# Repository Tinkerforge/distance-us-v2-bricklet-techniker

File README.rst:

Distance US Bricklet 2.0
========================

**This Bricklet is currently in development.**

This repository contains the firmware source code and the hardware design
files. The documentation generator configs can be found at
https://github.com/Tinkerforge/generators

Repository Content
------------------

software/:
 * examples/: Examples for all supported languages
 * build/: Compiled files
 * src/: Source code of firmware
 * Makefile: Makefile to build project

hardware/:
 * Contains KiCad project files and additionally schematics as PDF

datasheets/:
 * Contains datasheets for sensors and complex ICs that are used

Hardware
--------

The hardware is designed with the open source EDA Suite KiCad
(http://www.kicad.org). Before you are able to open the files,
you have to install the Tinkerforge kicad-libraries
(https://github.com/Tinkerforge/kicad-libraries). You can either clone
them directly in hardware/ or clone them in a separate folder and
symlink them into hardware/
(ln -s kicad_path/kicad-libraries project_path/hardware). After that you
can open the .pro file in hardware/ with KiCad and from there view and
modify the schematics and the PCB layout.

Software
--------

If you want to do your own Brick/Bricklet firmware development we highly
recommend that you use our build environment setup script and read the
tutorial (https://www.tinkerforge.com/en/doc/Tutorials/Tutorial_Build_Environment/Tutorial.html).

To compile the C code we recommend you to install the newest GNU Arm Embedded
Toolchain (https://launchpad.net/gcc-arm-embedded/+download).
You also need to install bricklib2 (https://github.com/Tinkerforge/bricklib2).

You can either clone it directly in software/src/ or clone it in a
separate folder and symlink it into software/src/
(ln -s bricklib_path/bricklib2 project_path/software/src/). Finally make sure to
have CMake installed (http://www.cmake.org/cmake/resources/software.html).

After that you can build the firmware by invoking make in software/.
The firmware (.zbin) can then be found in software/build/ and uploaded
with brickv (click button "Flashing" on start screen).

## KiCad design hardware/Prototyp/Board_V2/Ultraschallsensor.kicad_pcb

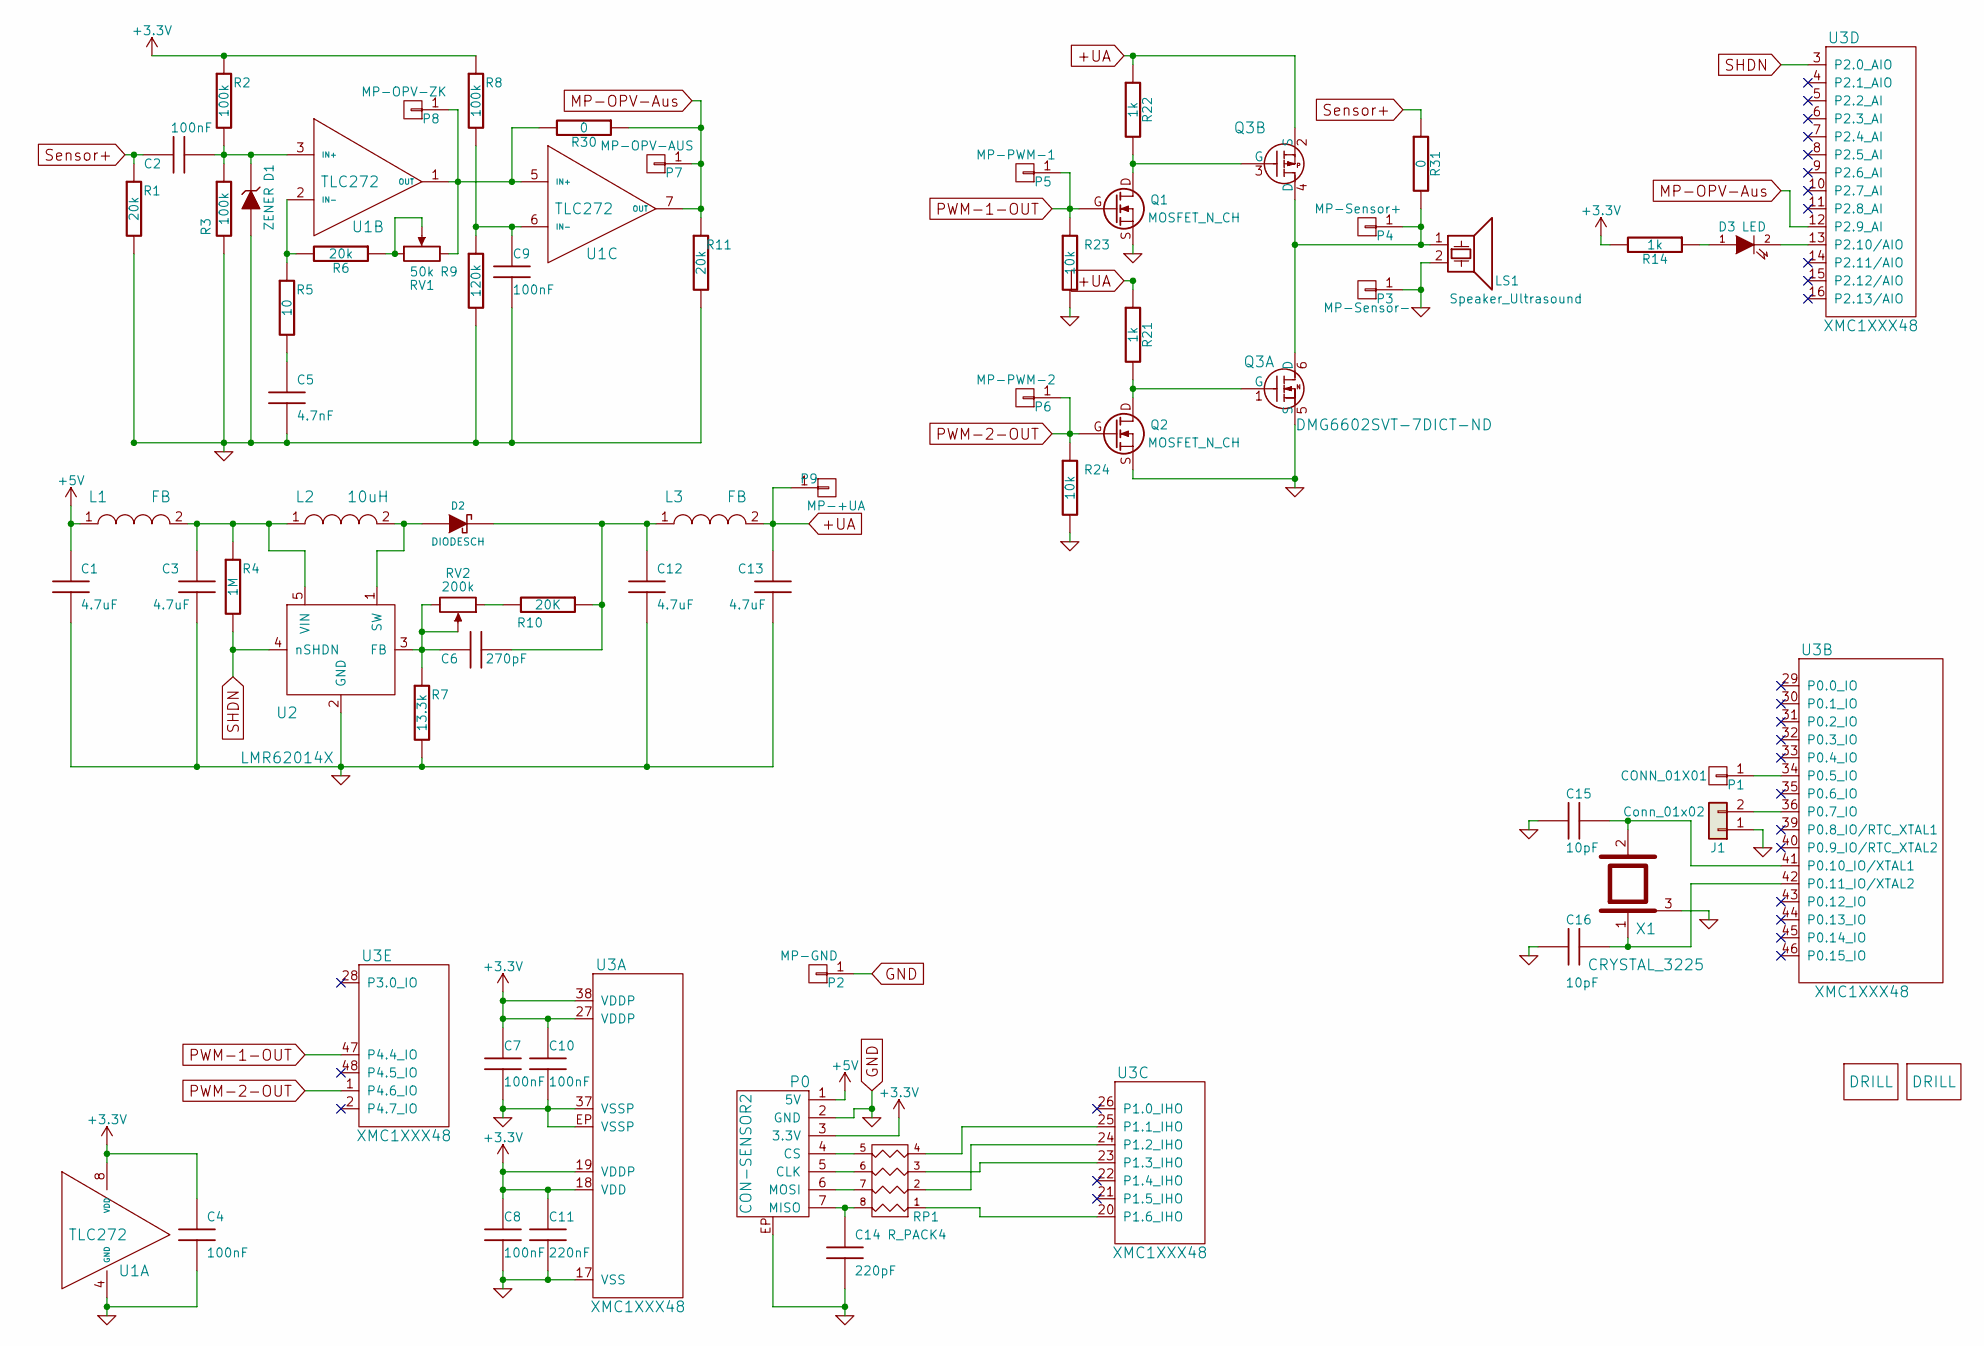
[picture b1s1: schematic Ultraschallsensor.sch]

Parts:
C1, C3, C12, C13: 4.7uF; C0805
C2, C4, C7, C8, C9, C10: 100nF; C0603F
C5: 4.7nF; C0603F
C6: 270pF; C0603F
C11: 220nF; C0603F
C14: 220pF; C0402F
C15, C16: 10pF; C0603F
D1: ZENER; SOD-123
D2: DIODESCH; SOD-123
D3: LED; D0603E
J1: Conn_01x02; SolderJumper
L1, L3: FB; C0603F
L2: 10uH; NR3030
LS1: Speaker_Ultrasound; PIN_ARRAY_2X1
P0: CON-SENSOR2
P1: CONN_01X01; CONN_1
P2: MP-GND; CONN_1
P3: MP-Sensor-; DEBUG_PAD
P4: MP-Sensor+; DEBUG_PAD
P5: MP-PWM-1; DEBUG_PAD
P6: MP-PWM-2; DEBUG_PAD
P7: MP-OPV-AUS; CONN_1
P8: MP-OPV-ZK; CONN_1
P9: MP-+UA; CONN_1
Q1, Q2: MOSFET_N_CH; SOT23GDS
Q3: DMG6602SVT-7DICT-ND; SOT23-6
R1, R6, R11: 20k; R0603F
R2, R3, R8: 100k; R0603F
R4: 1M; R0603F
R5: 10; R0603F
R7: 13.3k; R0603F
R9: 120k; R0603F
R10: 20K; R0603F
R14: 1k; R0603F
R21, R22: 1k; 1206E
R23, R24: 10k; R0603F
R30, R31: 0; R0603F
RP1: R_PACK4; 4X0402
RV1: 50k; ST4
RV2: 200k; ST4
U1: TLC272; TSSOP8
U2: LMR62014X; SOT23-5
U3: XMC1XXX48; QFN48-EP2
U4, U5: DRILL; DRILL_NP
X1: CRYSTAL_3225

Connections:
+3V3: C4.1, C7.1, C8.1, C10.1, C11.1, P0.3 (3.3V), R2.1, R8.1, R14.2, U1.8 (VDD), U3.18 (VDD), U3.19 (VDDP), U3.27 (VDDP), U3.38 (VDDP)
+5V: C1.1, L1.1, P0.1 (5V)
+UA: C13.1, L3.2, P9.1, Q3.2 (S), R21.1, R22.1
GND: C1.2, C3.2, C4.2, C5.2, C7.2, C8.2, C9.2, C10.2, C11.2, C12.2, C13.2, C14.2, C15.2, C16.2, D1.1 (A), J1.1, LS1.2, P0.2 (GND), P0.EP, P2.1, P3.1, Q1.S, Q2.S, Q3.5 (S), R1.2, R3.2, R7.2, R9.2, R11.2, R23.2, R24.2, U1.4 (GND), U2.2 (GND), U3.17 (VSS), U3.37 (VSSP), U3.EP (VSSP), X1.3
MP-OPV-Aus: P7.1, R11.1, R30.1, U1.7 (OUT), U3.12 (P2.9_AI)
unnamed: C2.1, D1.2 (K), R2.2, R3.1, U1.3 (IN+)
unnamed: C3.1, L1.2, L2.1, R4.1, U2.5 (VIN)
unnamed: C5.1, R5.2
unnamed: C6.2, R7.1, RV2.2, RV2.3, U2.3 (FB)
unnamed: C9.1, R8.2, R9.1, U1.6 (IN-)
unnamed: C6.1, C12.1, D2.2 (K), L3.1, R10.1
unnamed: C14.1, P0.7 (MISO), RP1.8 (R1)
unnamed: C15.1, U3.41 (P0.10_IO/XTAL1), X1.2
unnamed: C16.1, U3.42 (P0.11_IO/XTAL2), X1.1
unnamed: D2.1 (A), L2.2, U2.1 (SW)
unnamed: D3.1 (A), R14.1
unnamed: D3.2 (K), U3.13 (P2.10/AIO)
unnamed: J1.2, U3.36 (P0.7_IO)
unnamed: LS1.1, P4.1, Q3.4 (D), Q3.6 (D), R31.2
unnamed: P0.4 (CS), RP1.5 (R4)
unnamed: P0.5 (CLK), RP1.6 (R3)
unnamed: P0.6 (MOSI), RP1.7 (R2)
unnamed: P1.1, U3.34 (P0.5_IO)
unnamed: P8.1, R30.2, RV1.3, U1.1 (OUT), U1.5 (IN+)
unnamed: Q1.D, Q3.3 (G), R22.2
unnamed: Q2.D, Q3.1 (G), R21.2
unnamed: R5.1, R6.2, U1.2 (IN-)
unnamed: R6.1, RV1.1, RV1.2
unnamed: R10.2, RV2.1
unnamed: RP1.1, U3.20 (P1.6_IHO)
unnamed: RP1.2, U3.24 (P1.2_IHO)
unnamed: RP1.3, U3.23 (P1.3_IHO)
unnamed: RP1.4, U3.25 (P1.1_IHO)
PWM-1-OUT: P5.1, Q1.G, R23.1, U3.47 (P4.4_IO)
PWM-2-OUT: P6.1, Q2.G, R24.1, U3.1 (P4.6_IO)
SHDN: R4.2, U2.4 (nSHDN), U3.3 (P2.0_AIO)
Sensor+: C2.2, R1.1, R31.1

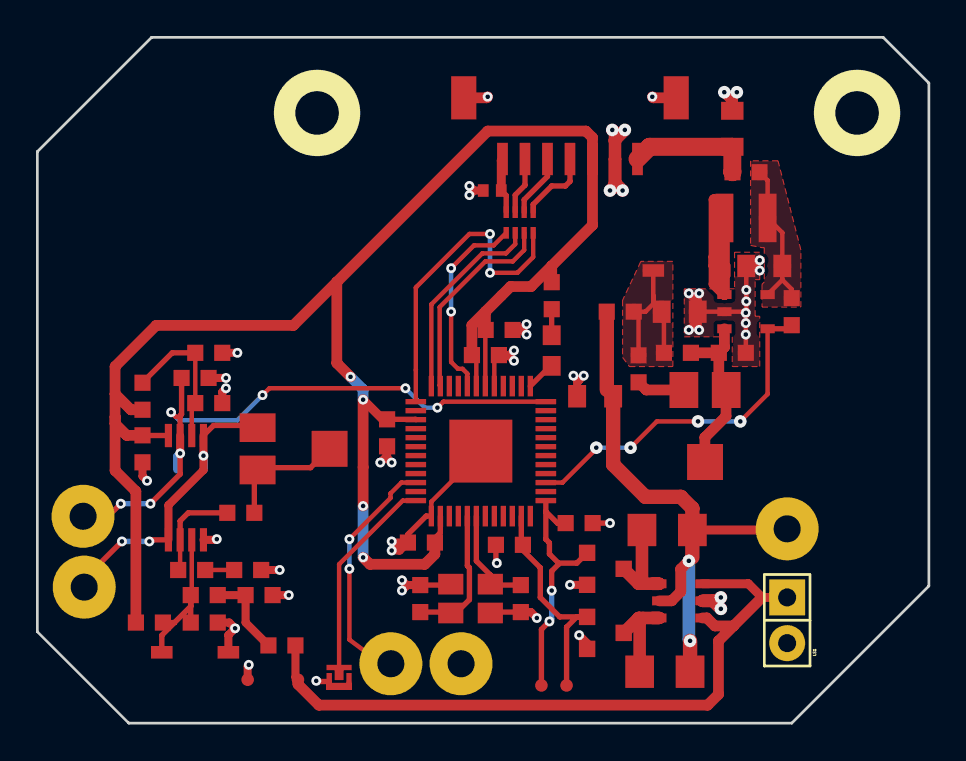
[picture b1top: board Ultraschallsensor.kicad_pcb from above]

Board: 2 copper layers, 49.5 x 38.1 mm, 64 parts (1 on the bottom side), 37 nets.

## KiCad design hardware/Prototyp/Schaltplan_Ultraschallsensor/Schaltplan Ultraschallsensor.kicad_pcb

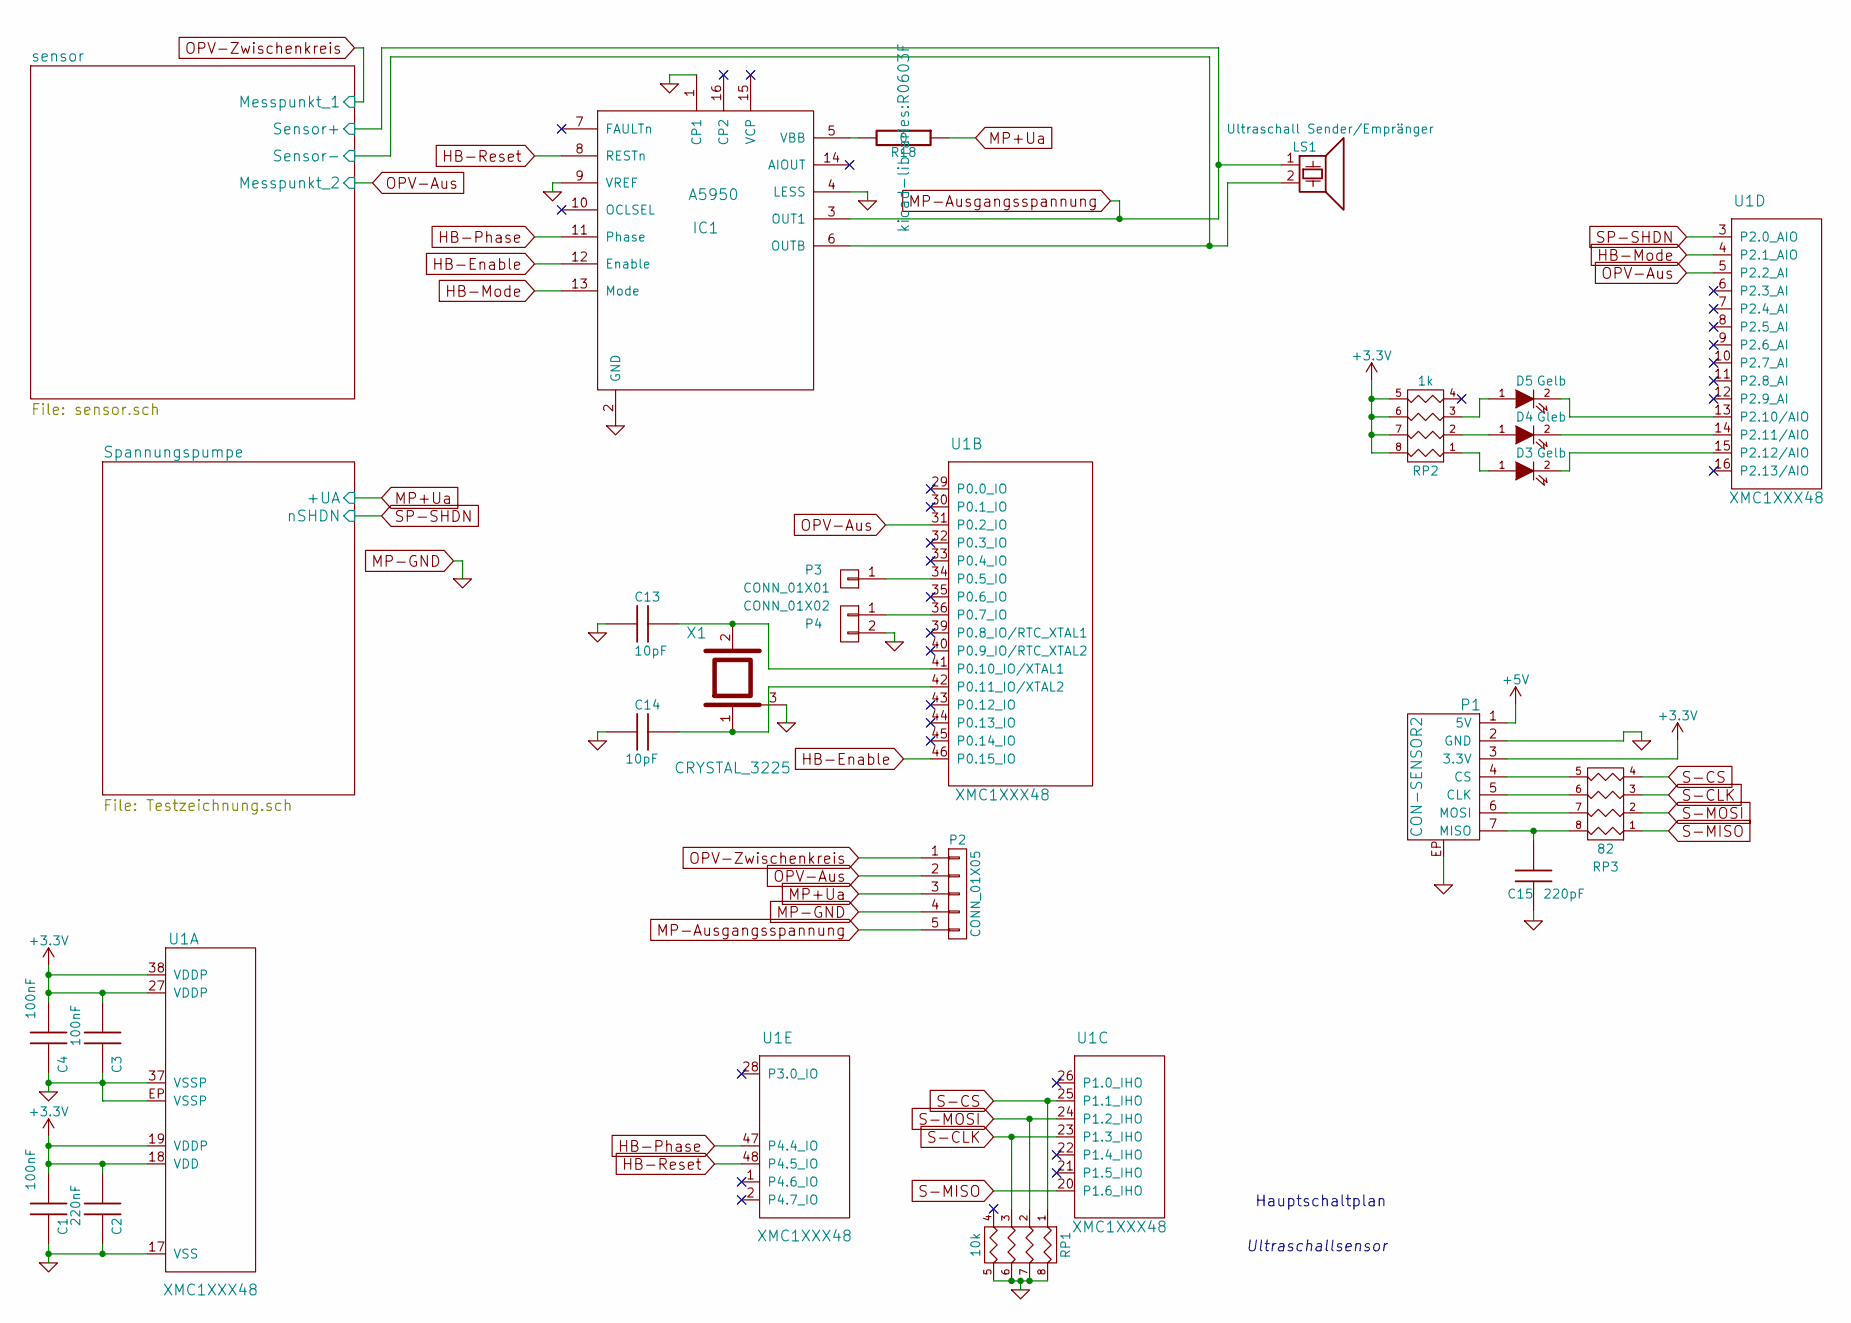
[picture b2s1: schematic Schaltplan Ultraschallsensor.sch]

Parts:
C1, C3, C4: 100nF; C0603F
C2: 220nF; C0603F
C13, C14: 10pF; C0603F
C15: 220pF; C0402F
D3, D5: Gelb; D0603E
D4: Gleb; D0603E
IC1: A5950; 16-leadTSSOP_0,137,4,4mmBreite
LS1: Ultraschall Sender/Empränger; Ultraschallsensor
P1: CON-SENSOR2
P2: CONN_01X05; pin_array_5x1
P3: CONN_01X01; DEBUG_PAD
P4: CONN_01X02; SolderJumper
R18: 0; R0603F
RP1: 10k; 0603X4
RP2: 1k; 0603X4
RP3: 82; 4X0402
U1: XMC1XXX48; QFN48-EP2
X1: CRYSTAL_3225

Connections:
+3V3: C1.1, C2.1, C3.1, C4.1, P1.3 (3.3V), RP2.5 (R4), RP2.6 (R3), RP2.7 (R2), RP2.8 (R1), U1.18 (VDD), U1.19 (VDDP), U1.27 (VDDP), U1.38 (VDDP); also elsewhere on the board
+5V: P1.1 (5V); also elsewhere on the board
HB-Enable: IC1.12 (Enable), U1.46 (P0.15_IO)
HB-Mode: IC1.13 (Mode), U1.4 (P2.1_AIO)
HB-Phase: IC1.11 (Phase), U1.47 (P4.4_IO)
HB-Reset: IC1.8 (RESTn), U1.48 (P4.5_IO)
MP+Ua: P2.3, R18.1; also elsewhere on the board
MP-Ausgangsspannung: IC1.3 (OUT1), LS1.1, P2.5; also elsewhere on the board
MP-GND: C1.2, C2.2, C3.2, C4.2, C13.2, C14.2, C15.2, IC1.1 (CP1), IC1.2 (GND), IC1.4 (LESS), IC1.6 (OUTB), IC1.9 (VREF), LS1.2, P1.2 (GND), P1.EP, P2.4, P4.2, RP1.5 (R4), RP1.6 (R3), RP1.7 (R2), RP1.8 (R1), U1.17 (VSS), U1.37 (VSSP), U1.EP (VSSP), X1.3; also elsewhere on the board
unnamed: C13.1, U1.41 (P0.10_IO/XTAL1), X1.2
unnamed: C14.1, U1.42 (P0.11_IO/XTAL2), X1.1
unnamed: C15.1, P1.7 (MISO), RP3.8 (R1)
unnamed: D3.1 (A), RP2.1
unnamed: D3.2 (K), U1.15 (P2.12/AIO)
unnamed: D4.1 (A), RP2.2
unnamed: D4.2 (K), U1.14 (P2.11/AIO)
unnamed: D5.1 (A), RP2.3
unnamed: D5.2 (K), U1.13 (P2.10/AIO)
unnamed: IC1.5 (VBB), R18.2
unnamed: P1.4 (CS), RP3.5 (R4)
unnamed: P1.5 (CLK), RP3.6 (R3)
unnamed: P1.6 (MOSI), RP3.7 (R2)
unnamed: P3.1, U1.34 (P0.5_IO)
unnamed: P4.1, U1.36 (P0.7_IO)
OPV-Aus: P2.2, U1.5 (P2.2_AI), U1.31 (P0.2_IO); also elsewhere on the board
OPV-Zwischenkreis: P2.1; also elsewhere on the board
S-CLK: RP1.3, RP3.3, U1.23 (P1.3_IHO)
S-CS: RP1.1, RP3.4, U1.25 (P1.1_IHO)
S-MISO: RP3.1, U1.20 (P1.6_IHO)
S-MOSI: RP1.2, RP3.2, U1.24 (P1.2_IHO)
SP-SHDN: U1.3 (P2.0_AIO); also elsewhere on the board

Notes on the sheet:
Ultraschallsensor
Hauptschaltplan

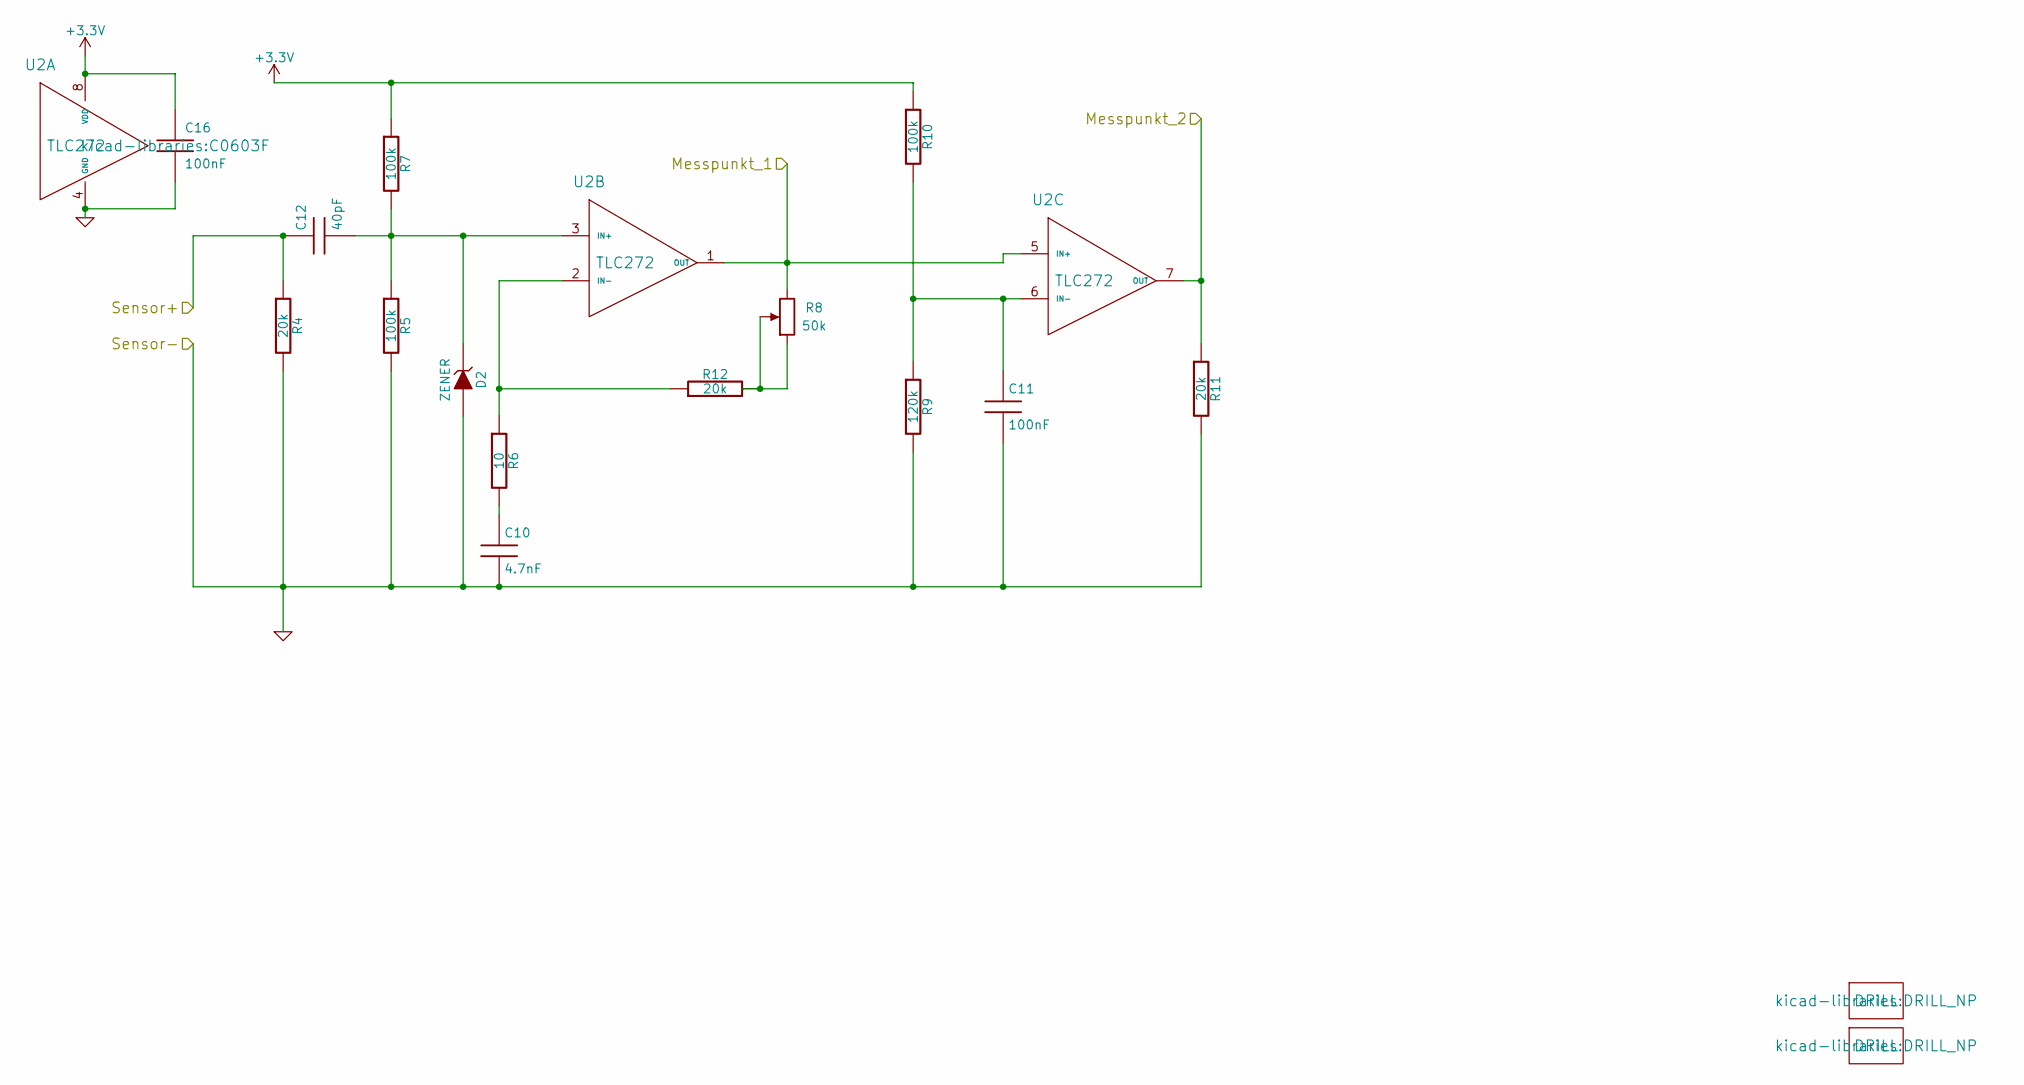
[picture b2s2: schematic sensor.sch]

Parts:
C10: 4.7nF; C0603F
C11, C16: 100nF; C0603F
C12: 40pF; C0603F
D2: ZENER; SOD-123
R4, R11, R12: 20k; R0603F
R5, R7, R10: 100k; R0603F
R6: 10; R0603F
R8: 50k; ST4ETA
R9: 120k; R0603F
U2: TLC272; TSSOP8
U5, U6: DRILL; DRILL_NP

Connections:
+3V3: C16.1, R7.1, R10.1, U2.8 (VDD); also elsewhere on the board
MP-Ausgangsspannung: C12.1, R4.1; also elsewhere on the board
MP-GND: C10.2, C11.2, C16.2, D2.1 (A), R4.2, R5.2, R9.2, R11.2, U2.4 (GND); also elsewhere on the board
unnamed: C10.1, R6.2
unnamed: C11.1, R9.1, R10.2, U2.6 (IN-)
unnamed: C12.2, D2.2 (K), R5.1, R7.2, U2.3 (IN+)
unnamed: R6.1, R12.1, U2.2 (IN-)
unnamed: R8.1, R8.2, R12.2
OPV-Aus: R11.1, U2.7 (OUT); also elsewhere on the board
OPV-Zwischenkreis: R8.3, U2.1 (OUT), U2.5 (IN+); also elsewhere on the board

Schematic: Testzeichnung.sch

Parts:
C5, C6, C7, C8: 4.7uF; C0603F
C9: 270pF; C0603F
D1: B0520LW; SOD-123F
L1, L3: FB; 0603F
L2: 10uH; 0603F
R1: 0-200K; ST4ETA
R2: 13.3k; R0603F
R3: 1M; R0603F
R13: 20k; R0603F
U3: LMR62014X; SOT23-5

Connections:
MP+Ua: C7.1, L3.2; also elsewhere on the board
MP-GND: C5.2, C6.2, C7.2, C8.2, R2.2, U3.2 (GND); also elsewhere on the board
unnamed 9: C5.1, L1.1; also elsewhere on the board
unnamed: C6.1, L1.2, L2.1, R3.1, U3.5 (VIN)
unnamed: C8.1, C9.2, D1.1 (K), L3.1, R13.1
unnamed 12: C9.1, R2.1, U3.3 (FB); also elsewhere on the board
unnamed: D1.2 (A), L2.2, U3.1 (SW)
unnamed 39: R13.2; also elsewhere on the board
SP-SHDN: R3.2, U3.4 (nSHDN); also elsewhere on the board

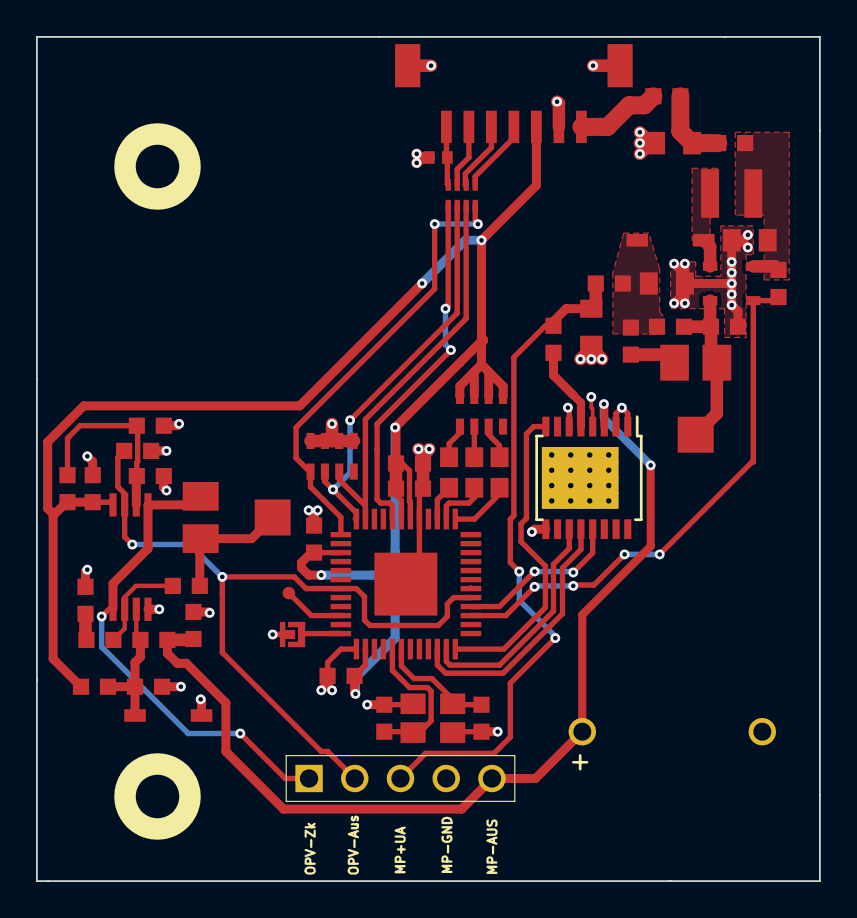
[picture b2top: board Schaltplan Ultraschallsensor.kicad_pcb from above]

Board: 2 copper layers, 43.5 x 46.9 mm, 54 parts (0 on the bottom side), 42 nets.

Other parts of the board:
R17: 0; R0603F
RV1: 200k; ST4ETA

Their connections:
+5V: R17.1; also elsewhere on the board
unnamed 9: R17.2; also elsewhere on the board
unnamed 12: RV1.2, RV1.3; also elsewhere on the board
unnamed 39: RV1.1; also elsewhere on the board

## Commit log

2018-01-03 This is a test
2018-02-01 Comit-Nachricht
2018-02-01 Commit-Nachricht
2018-02-01 test
2018-02-01 richtig
2018-02-01 richt
2018-02-01 Änderung an Vokabeln
2018-02-01 dein misst gelöscht
2018-02-01 Neuer Inhalt
2018-02-01 Neues Daten
2018-02-01 neue Version
2018-02-02 Lösche K
2018-02-02 Lösche Schaltplan
2018-02-02 Lösche sensor
2018-02-02 lösche schaltplan_ultraschallsensor
2018-02-02 Lösche Schaltplan_Ultraschall
2018-02-02 Lösche
2018-02-02 An TF angepasst
2018-02-02 Schaltplanaktualisierung
2018-02-02 Tutorial
2018-02-02 Namensänderung von Tutorial
2018-02-02 Änderung am Tut
2018-02-02 Änderung an Tutorial
2018-02-02 Platinenlayout
2018-02-05 Add stub software implementation for Distance US Bricklet 2.0
2018-02-05 Add gitignore
2018-02-05 Fix status and boot pad pins
2018-02-05 Add stub tick/init for a16pt
2018-02-05 Use correct flash size
2018-02-05 Layout
2018-02-05 ändern bei änderung einer Datei
2018-02-06 Tutorial_bearbeitet
2018-02-07 Befestigungen
2018-02-07 main
2018-02-07 korrekturPCB
2018-02-08 änderung
2018-02-08 Aktueller Stand
2018-02-08 Neue Soft
2018-02-12 Pull_Up
2018-02-12 Bauteilliste
2018-02-12 struktogramme
2018-02-14 Timer_Service
2018-02-14 Defines für den US sensor fertig
2018-02-15 kommentare
2018-02-15 ERU_izz_da
2018-02-19 Neue Ordner und Software
2018-02-19 Use correct shadow transfers, make sure that wie use slice number as integer instead of pointer if necessary, add proper indentation
2018-02-19 Use proper indentation
2018-02-19 Configure frequency for 1khz
2018-02-19 Add 250ms intervals for debugging of CCU40 slices
2018-02-19 Start pwm timer every 33ms (30 measurements per second)
2018-02-19 Use proper init ordering
2018-02-19 Stop slice 0 if slice interrupt occurs (10x edge alternation of PWM)
2018-02-22 Use correct pins for boot pad and status led
2018-02-23 Test_lauf_1
2018-02-23 CCU4_wechsel
2018-02-26 Dokumentation
2018-03-01 software
2018-03-02 HardwareV2
2018-03-02 HardwareV2b
2018-03-02 Update_Hardware
2018-03-02 set clearance to 0
2018-03-05 Remove unused flash-size define
2018-03-05 update documentation
2018-03-06 doku
2018-03-06 Aktueller Software STand
2018-03-06 Add define for gap between PWM. The high side/low side switch are not allowed to be turned on at the same time, so we add a small gap between the PWM peaks to make sure that we never have a short cir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
2018-03-06 Refactor pwm config function, so the function can be properly called with different slice numberes again
2018-03-06 When we want to stop the PWM, we have to make sure that the "high peak" of the second PWM runs completely through before we stop it. Otherwise we get 10 peaks on the low side switch but only 9.5 peak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
2018-03-06 Put slice independent configurations and configurations that are not done for every PWM in the init function directly
2018-03-06 Start timer CCUs synchronously through SCU with high trigger
2018-03-06 Remove now unnecessary gpio init
2018-03-06 Before start clear slice 0 and initialize slice 2 with compare value, so we get the offsets between the PWMs.
2018-03-07 neu soft
2018-03-08 Korrektur pcb
2018-03-12 Messungen
2018-03-13 Add files via upload
    Neue Dokudokument
2018-03-14 Add files via upload
    Emfänger bearbeitet
2018-03-14 Empfänger
2018-03-14 Add files via upload
    Jo
2018-03-14 Add files via upload
    Neue Texte
2018-03-14 Verwendete Bauteile Update
2018-03-14 Add files via upload
    Neue Struktur und Text
2018-03-15 Schaltplan_update
2018-03-15 Änderung an der Überschrift 2.3
2018-03-15 Schaltplan_update2.0
2018-03-15 Add files via upload
    XMC Infinoen Hinzugefügt bei den Quellen
2018-03-15 Add files via upload
    Controller Link entfernt
2018-03-15 Add files via upload
    Änderung
2018-03-15 a16pt_update
2018-03-15 Abbildungen
2018-03-15 Neue änderung
2018-03-15 neues unter Kapitel
2018-03-15 Richtiger Stand
2018-03-15 Add files via upload
    Extrea Kaptiel Besonderheit der Software
2018-03-15 Add files via upload
    Programm abschnitt bei Interrupt richtig geändert
2018-03-16 Add files via upload
    BUg Beseitig
2018-03-16 Add files via upload
    Neue Bilder für den Sender
2018-03-16 Add files via upload
    Sender Auswertung
2018-03-16 Add files via upload
    Texte optimiert
2018-03-16 Add files via upload
    Mein Part izz da
2018-03-16 Add files via upload
    Filterschaltung sowie Hochsetzsteler bearbeitet
2018-03-17 Add files via upload
    Erste Korrekturen wurden vorgenommen und eine Überschrift angepasst
2018-03-18 Add files via upload
    Weitere Korrekturen sowie eine neue Überschrift für das Open Source Kapitel
2018-03-19 Messwerttabelle
2018-03-19 Add files via upload
    Um die Init erweiter usw.
2018-03-19 korrektur
2018-03-19 Add files via upload
    SOftware Doku überarbeitet
2018-03-19 Add files via upload
    Feinheiten vorgenommen
2018-03-20 vorabversion
2018-03-20 Add files via upload
    Tabelle izz da
2018-03-20 Update 8_Messungen.tex
    "im Laufe"
2018-03-20 Update 7_Entwicklung_der_Software.tex
    Geschützte Leerzeichen Hinzugefügt "~"
2018-03-20 Update 8_Messungen.tex
    Geschützte Leerzeichen hinzugefügt "~"
2018-03-20 Update 5_Verwendete_Bauteile.tex
    Geschützte Leerzeichen hinzugefügt "~"
2018-03-20 Update 10_Fazit_Auftraggeber.tex
    aus "mach" wird "ist" im letzten Satz
2018-03-21 bilder bearbeitet
2018-03-21 4und10
2018-03-21 schema
2018-03-22 Zusammenfassung
2018-03-22 reflexion
2018-03-22 abbildung
2018-03-22 quellcode
2018-03-22 texte
2018-03-23 finale Dokumentation
2018-04-18 Schaltplan Korrektur
2018-06-06 Adapt to bricklib2 callback-value changes to fix wrong length of get-distance packet
2018-06-28 Fix readme
2018-07-11 Add Makefile with docker support
2018-07-11 Update directory structure and build instructions
2018-07-11 Remove obsolete generate_makefile scripts
2021-10-25 Update KiCad link
    https://www.kicad.org/blog/2021/10/Avoid-links-to-former-kicad-domain/
